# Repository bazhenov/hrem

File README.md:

# HREM

This project contains firware code and KiCad schematics/PCB files for simple door latch reminder.

## The problem

Me and my wife forget to close our flat entrance door from time to time. What will you do about that? :)

This project is simple hardware solution to remind us about open door. It's not the simplest nor most elegant solution, but more like excuse for practicing skills in embedded software development and electrical engineering.

## The solution

Solution is quite simple:

1. door latch has magnet on it's end;
1. hall effect sensor integrated into door frame right near latch with magnet;
1. μC powering up hall sensor once in a while and check magnet presense (hence door is closed);
1. buzzer goes on if latch is open.

## Part list

Complete BOM is in project files, but here are key parts used in a project:

1. [ATTiny85] as a μC
1. [Honeywell SS49][SS19] hall effect sensor;
1. [HT7733] as a voltage boost up controller. Single AAA battery is required.

## Building firmware

You need to have standart AVR toolchain is installed (e.g. `avr-gcc`, `avr-objcopy`...). Beyond that building firmware is as simple as:

```
$ make
```

[SS19]: https://eu.mouser.com/datasheet/2/187/SS49-1168552.pdf
[HT7733]: https://img.ozdisan.com/ETicaret_Dosya/349361_8060324.pdf
[attiny85]: https://ww1.microchip.com/downloads/en/DeviceDoc/Atmel-2586-AVR-8-bit-Microcontroller-ATtiny25-ATtiny45-ATtiny85_Datasheet.pdf

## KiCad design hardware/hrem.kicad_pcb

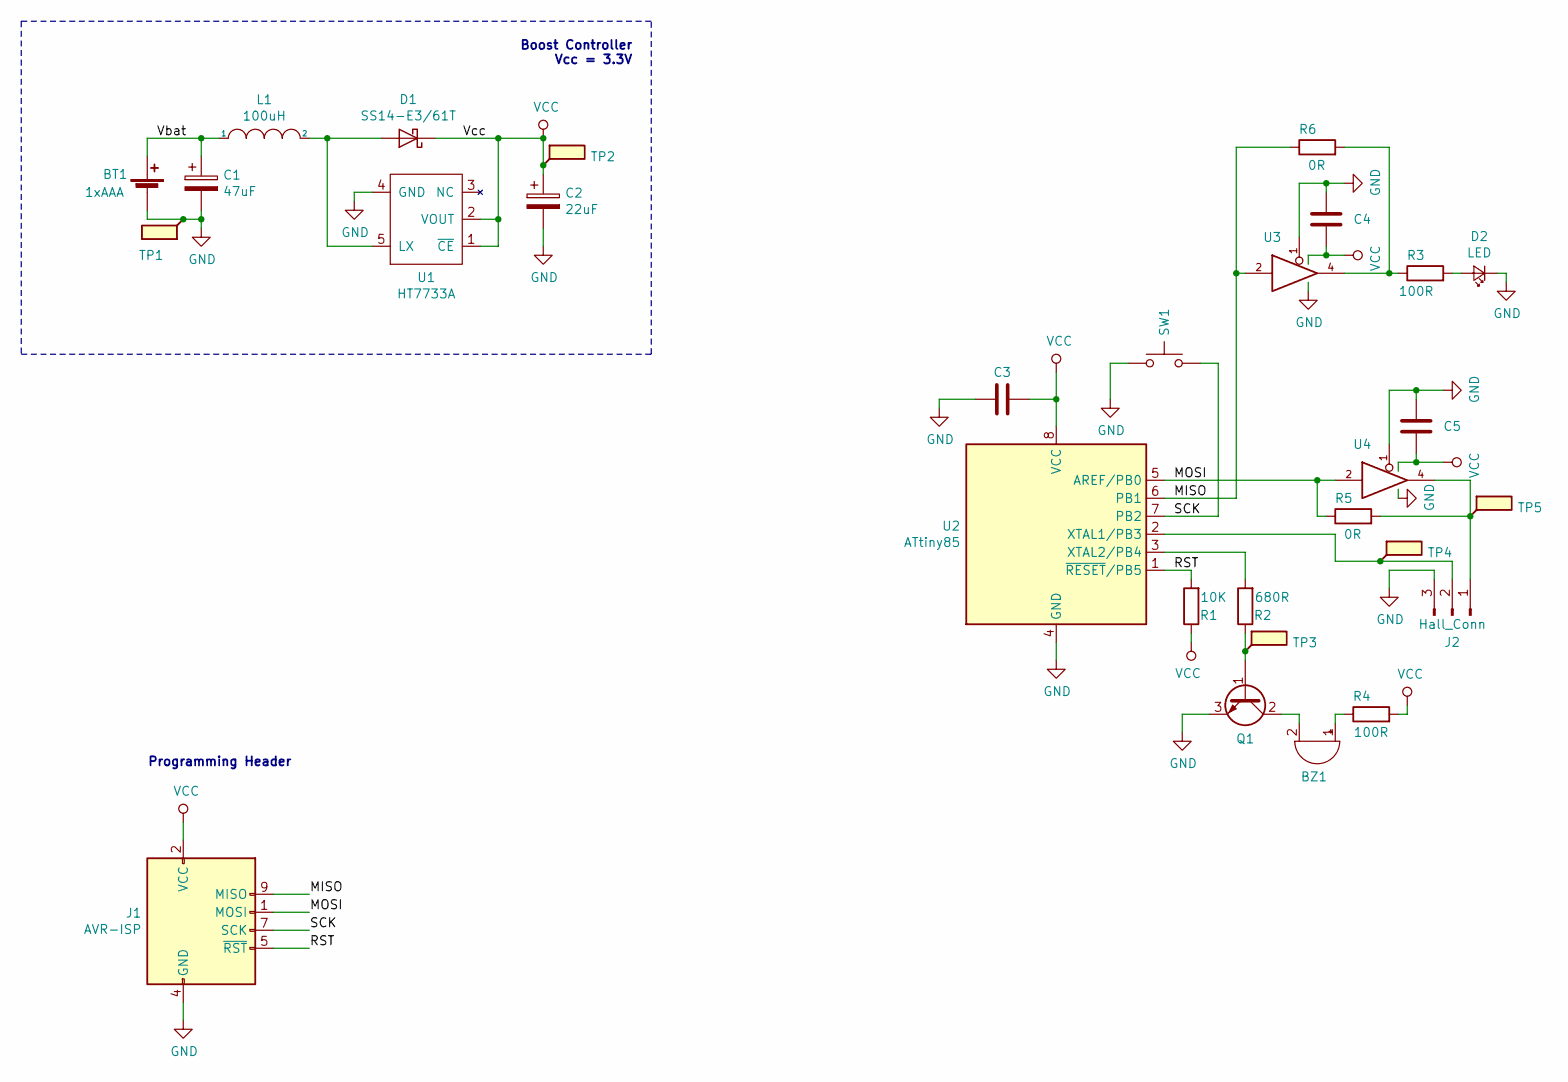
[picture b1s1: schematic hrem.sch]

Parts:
BT1: 1xAAA; AAA battery
BZ1: Buzzer; buzzer
C1: 47uF; CP_EIA-3528-15_AVX-H_Pad1.50x2.35mm_HandSolder; Part C22036
C2: 22uF; CP_EIA-3528-15_AVX-H_Pad1.50x2.35mm_HandSolder; Part C7198
C3, C4, C5: 100nF; C_0805_2012Metric_Pad1.15x1.40mm_HandSolder; Part C354369
D1: SS14-E3/61T; D_SMA_Handsoldering; Part C47460
D2: LED; LED_D3.0mm
J1: AVR-ISP; IDC-Header_2x05_P2.54mm_Vertical
J2: Hall_Conn; X8821WRS-03-9TSN; Part C397433
L1: 100uH; Murata LQH43; Part C113087
Q1: MMBT4401-7-F; SOT-23_Handsoldering; Part C151826
R1: 10K; R_0805_2012Metric_Pad1.15x1.40mm_HandSolder; Part C103904
R2: 680R; R_0805_2012Metric_Pad1.15x1.40mm_HandSolder; Part C410034
R3, R4: 100R; R_0805_2012Metric_Pad1.15x1.40mm_HandSolder; Part C193990
R5, R6: 0R; R_0805_2012Metric_Pad1.15x1.40mm_HandSolder; Part C465486
SW1: SW_Push_Dual; Diptronics DTSM-65N; Part C224982
TP1: TestPoint_Flag; TestPoint_Loop_D2.50mm_Drill1.0mm
TP2, TP3, TP4, TP5: TestPoint_Flag; TestPoint_Pad_D2.0mm
U1: HT7733A; SOT-23-5_HandSoldering
U2: ATtiny85; SOIC-8_5.23x5.23mm_P1.27mm
U3, U4: 74LVC1G125; SOT-23-5_HandSoldering; Part C23654

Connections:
/MISO: J1.9 (MISO), R6.1, U2.6 (PB1), U3.2
/MOSI: J1.1 (MOSI), R5.1, U2.5 (AREF/PB0), U4.2
/RST: J1.5 (~RST), R1.2, U2.1 (~RESET~/PB5)
/SCK: J1.7 (SCK), SW1.2, U2.7 (PB2)
/Vbat: BT1.1 (+), C1.1, L1.1
GND: BT1.2 (-), C1.2, C2.2, C3.2, C4.2, C5.2, D2.1 (K), J1.4 (GND), J1.6 (GND), J1.8 (GND), J1.10 (GND), J2.3, Q1.3 (E), SW1.1, TP1.1, U1.4 (GND), U2.4 (GND), U3.1, U3.3 (GND), U4.1, U4.3 (GND)
unnamed: BZ1.1 (-), R4.1
unnamed: BZ1.2 (+), Q1.2 (C)
unnamed: D1.2 (A), L1.2, U1.5 (LX)
unnamed: D2.2 (A), R3.2
unnamed: J2.1, R5.2, TP5.1, U4.4
unnamed: J2.2, TP4.1, U2.2 (XTAL1/PB3)
unnamed: Q1.1 (B), R2.1, TP3.1
unnamed: R2.2, U2.3 (XTAL2/PB4)
unnamed: R3.1, R6.2, U3.4
VCC: C2.1, C3.1, C4.1, C5.1, D1.1 (K), J1.2 (VCC), R1.1, R4.2, TP2.1, U1.1 (~CE), U1.2 (VOUT), U2.8 (VCC), U3.5 (VCC), U4.5 (VCC)

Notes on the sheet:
Boost Controller Vcc = 3.3V
Programming Header

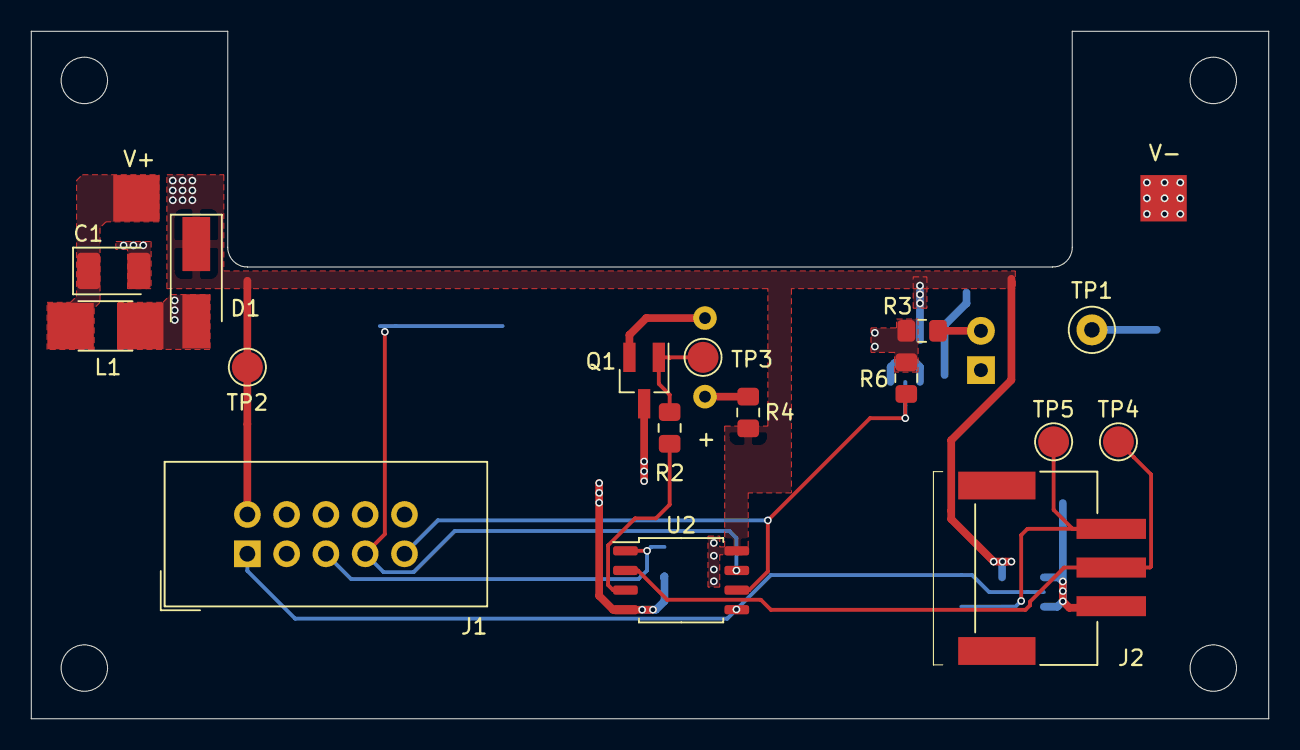
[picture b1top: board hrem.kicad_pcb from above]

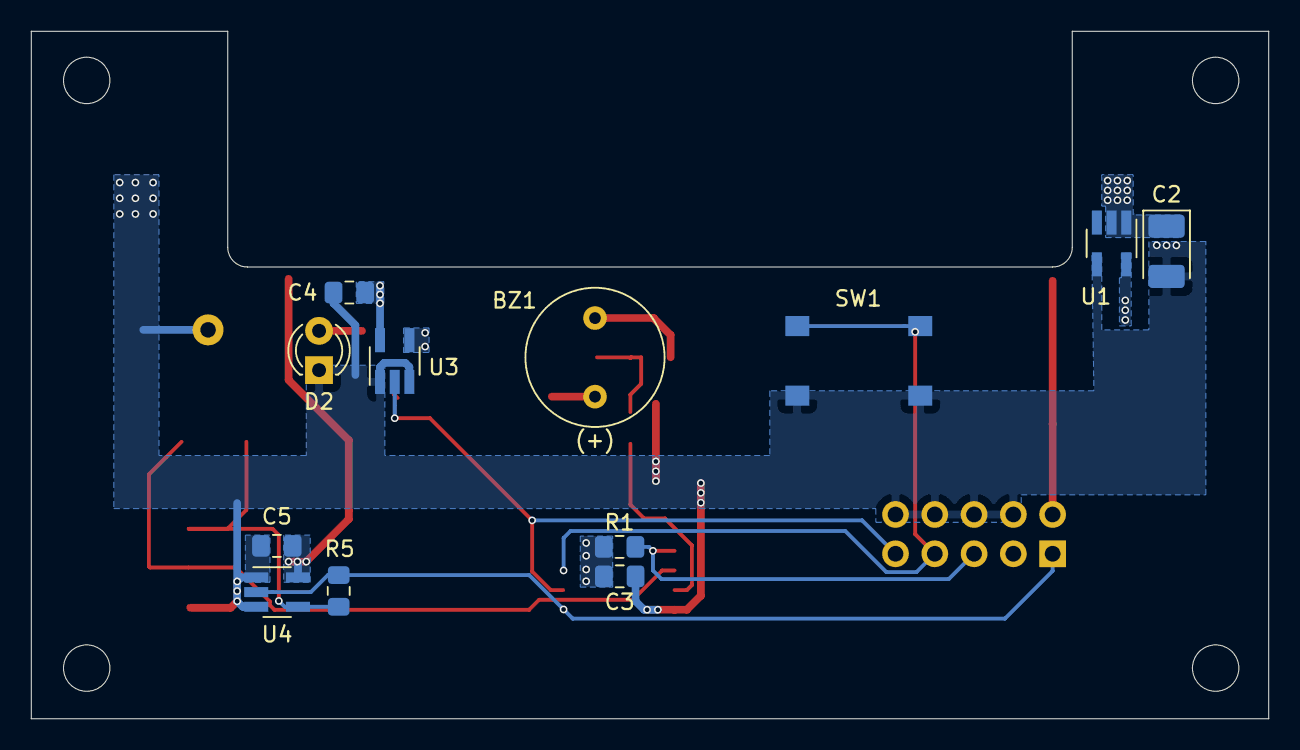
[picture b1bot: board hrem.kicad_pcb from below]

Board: 2 copper layers, 80.0 x 44.4 mm, 29 parts (12 on the bottom side), 16 nets.

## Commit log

2016-03-14 Первая рабочая версия
2016-03-14 Добавил bin/hex файлы в gitignore
2016-03-14 Поддержка индикаторного светодиода
2016-03-15 Sleep mode added
2016-03-31 Первый рабочий прототип
2016-03-31 Удалил ненужные файлы
2016-05-02 PCB improvements
2016-06-19 SMD version
2016-10-23 Project canges
2019-10-12 prototype of new version is commited
2019-10-19 hardware changes
2019-10-26 Some changes to schematics
2019-11-23 Makefile now correctly tracks source changes
2019-11-23 Enabled INT0
2019-11-24 Using standart bit manipulating idioms rather than own macros
2019-11-24 New rev
2020-01-02 Migration to new KiCad version
2020-01-03 Added backup files under gitignore
2020-01-03 Update ICSP footprint information
2020-01-03 Moved to a cpp
2020-01-03 buzzer fixed
2020-01-05 Firmware size reporting added
2020-01-05 Moved to multibinary makefile using CPP
2020-01-05 Various imrovements
    - C++ templates are used to isolate pin management
    - flash-* targets are renamed to *.flash to improve shell experience
2020-01-05 LongPress implemented for Button
2020-01-06 Register acces functions moved to a separate struct
2020-01-06 DigitalOutput::strobe() method added
2020-01-06 Base poll loop implemented
2020-01-07 Template ompimizations
2020-01-09 Working version
2020-01-12 KiCad new footprints
2020-01-17 Footprint change
2020-01-19 Work over schematics
2020-01-19 Button footprint added
2020-01-19 Boosting voltage regulator pcb layout
2020-01-20 Buzzer and LED PCB layout
2020-02-01 Work on PCB layout
2020-02-01 PCB layout all set
2020-02-02 Buzzer PCB layout dimensions fixed
2020-02-02 PCB tracks cleanup
2020-02-02 Replace 68R with 100R on LED for component unification purposes (15mA current)
2020-02-02 PCB POWER trace for BZ1 and D2
2020-02-02 Decoupling caps added on U3 and U4
2020-02-02 Schematic cleanup
2020-02-02 Revision updated on shcematics
2020-02-02 PCB ref names positioning and vendor part names
2020-02-09 First fabrication version
2020-03-16 simavr emulation toolchain added
2020-04-17 Fixed layout issue
    Q1 has invalid schematics symbol. Base and collector was swaped.
2020-04-18 Remove old files
2020-04-18 README added
2020-04-18 Firmware building instructions added
2020-04-18 Create LICENSE
2020-04-18 Testing GHA
2020-04-18 Implementing GitHub Actions
    https://github.com/marketplace/actions/avr-make is used as build action
2020-04-18 Update README.md
    Add CI status badge
2020-04-18 Rename workflow
2020-04-18 Update CI-badge
2020-04-18 Publishing firmware artifacts to GHA (#2)
    * Update main.yml
    * Rename workflow
    * Update CI-badge
2020-04-18 typo

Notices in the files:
parts and their libraries:
SparkFun-Resistors: Licensing: Creative Commons ShareAlike 4.0 International - https://creativecommons.org/licenses/by-sa/4.0
